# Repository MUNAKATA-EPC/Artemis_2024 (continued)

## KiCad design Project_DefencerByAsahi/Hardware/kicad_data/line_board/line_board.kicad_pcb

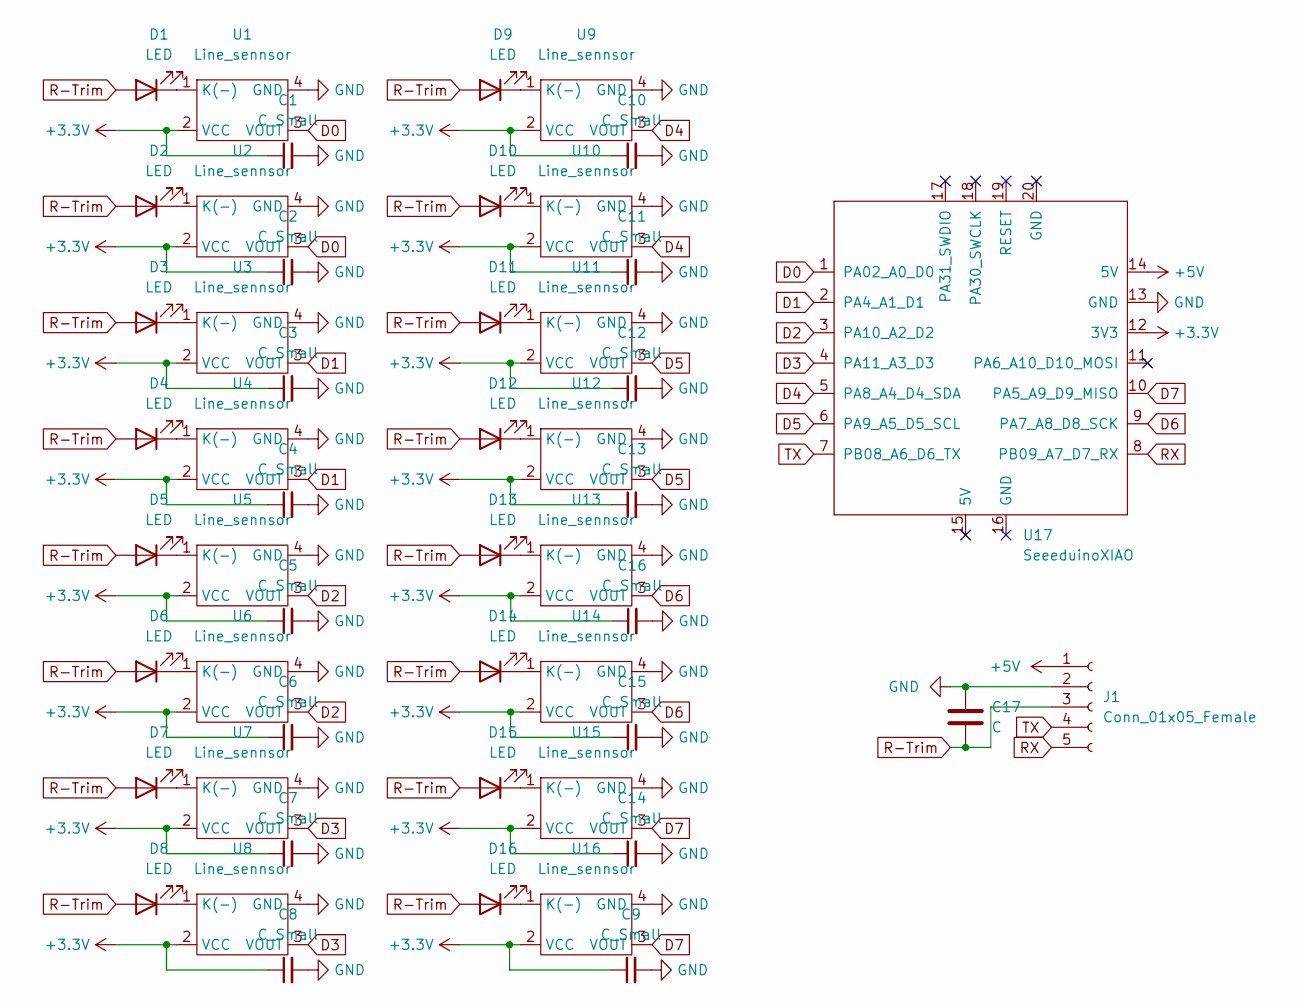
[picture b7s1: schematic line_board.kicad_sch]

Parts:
C1, C2, C3, C4, C5, C6, C7, C8, C9, C10, C11, C12, C13, C14, C15, C16: C_Small; C_Disc_D3.8mm_W2.6mm_P2.50mm
C17: C; CP_Radial_D5.0mm_P2.50mm
D1, D2, D3, D4, D5, D6, D7, D8, D9, D10, D11, D12, D13, D14, D15, D16: LED; LED_D3.0mm_Clear
J1: Conn_01x05_Female; JST_XH_B5B-XH-A_1x05_P2.50mm_Vertical
U1, U2, U3, U4, U5, U6, U7, U8, U9, U10, U11, U12, U13, U14, U15, U16: Line_sennsor; Line_Sensor
U17: SeeeduinoXIAO; seeeduinoXIAO

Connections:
+3.3V: C1.1, C2.1, C3.1, C4.1, C5.1, C6.1, C7.1, C8.1, C9.1, C10.1, C11.1, C12.1, C13.1, C14.1, C15.1, C16.1, U1.2 (VCC), U2.2 (VCC), U3.2 (VCC), U4.2 (VCC), U5.2 (VCC), U6.2 (VCC), U7.2 (VCC), U8.2 (VCC), U9.2 (VCC), U10.2 (VCC), U11.2 (VCC), U12.2 (VCC), U13.2 (VCC), U14.2 (VCC), U15.2 (VCC), U16.2 (VCC), U17.12 (3V3)
+5V: J1.1, U17.14 (5V)
D0: U1.3 (VOUT), U2.3 (VOUT), U17.1 (PA02_A0_D0)
D1: U3.3 (VOUT), U4.3 (VOUT), U17.2 (PA4_A1_D1)
D2: U5.3 (VOUT), U6.3 (VOUT), U17.3 (PA10_A2_D2)
D3: U7.3 (VOUT), U8.3 (VOUT), U17.4 (PA11_A3_D3)
D4: U9.3 (VOUT), U10.3 (VOUT), U17.5 (PA8_A4_D4_SDA)
D5: U11.3 (VOUT), U12.3 (VOUT), U17.6 (PA9_A5_D5_SCL)
D6: U13.3 (VOUT), U14.3 (VOUT), U17.9 (PA7_A8_D8_SCK)
D7: U15.3 (VOUT), U16.3 (VOUT), U17.10 (PA5_A9_D9_MISO)
GND: C1.2, C2.2, C3.2, C4.2, C5.2, C6.2, C7.2, C8.2, C9.2, C10.2, C11.2, C12.2, C13.2, C14.2, C15.2, C16.2, C17.1, J1.2, U1.4 (GND), U2.4 (GND), U3.4 (GND), U4.4 (GND), U5.4 (GND), U6.4 (GND), U7.4 (GND), U8.4 (GND), U9.4 (GND), U10.4 (GND), U11.4 (GND), U12.4 (GND), U13.4 (GND), U14.4 (GND), U15.4 (GND), U16.4 (GND), U17.13 (GND)
unnamed: D1.1 (K), U1.1 (K(-))
unnamed: D2.1 (K), U2.1 (K(-))
unnamed: D3.1 (K), U3.1 (K(-))
unnamed: D4.1 (K), U4.1 (K(-))
unnamed: D5.1 (K), U5.1 (K(-))
unnamed: D6.1 (K), U6.1 (K(-))
unnamed: D7.1 (K), U7.1 (K(-))
unnamed: D8.1 (K), U8.1 (K(-))
unnamed: D9.1 (K), U9.1 (K(-))
unnamed: D10.1 (K), U10.1 (K(-))
unnamed: D11.1 (K), U11.1 (K(-))
unnamed: D12.1 (K), U12.1 (K(-))
unnamed: D13.1 (K), U13.1 (K(-))
unnamed: D14.1 (K), U14.1 (K(-))
unnamed: D15.1 (K), U15.1 (K(-))
unnamed: D16.1 (K), U16.1 (K(-))
R-Trim: C17.2, D1.2 (A), D2.2 (A), D3.2 (A), D4.2 (A), D5.2 (A), D6.2 (A), D7.2 (A), D8.2 (A), D9.2 (A), D10.2 (A), D11.2 (A), D12.2 (A), D13.2 (A), D14.2 (A), D15.2 (A), D16.2 (A), J1.3
RX: J1.5, U17.8 (PB09_A7_D7_RX)
TX: J1.4, U17.7 (PB08_A6_D6_TX)

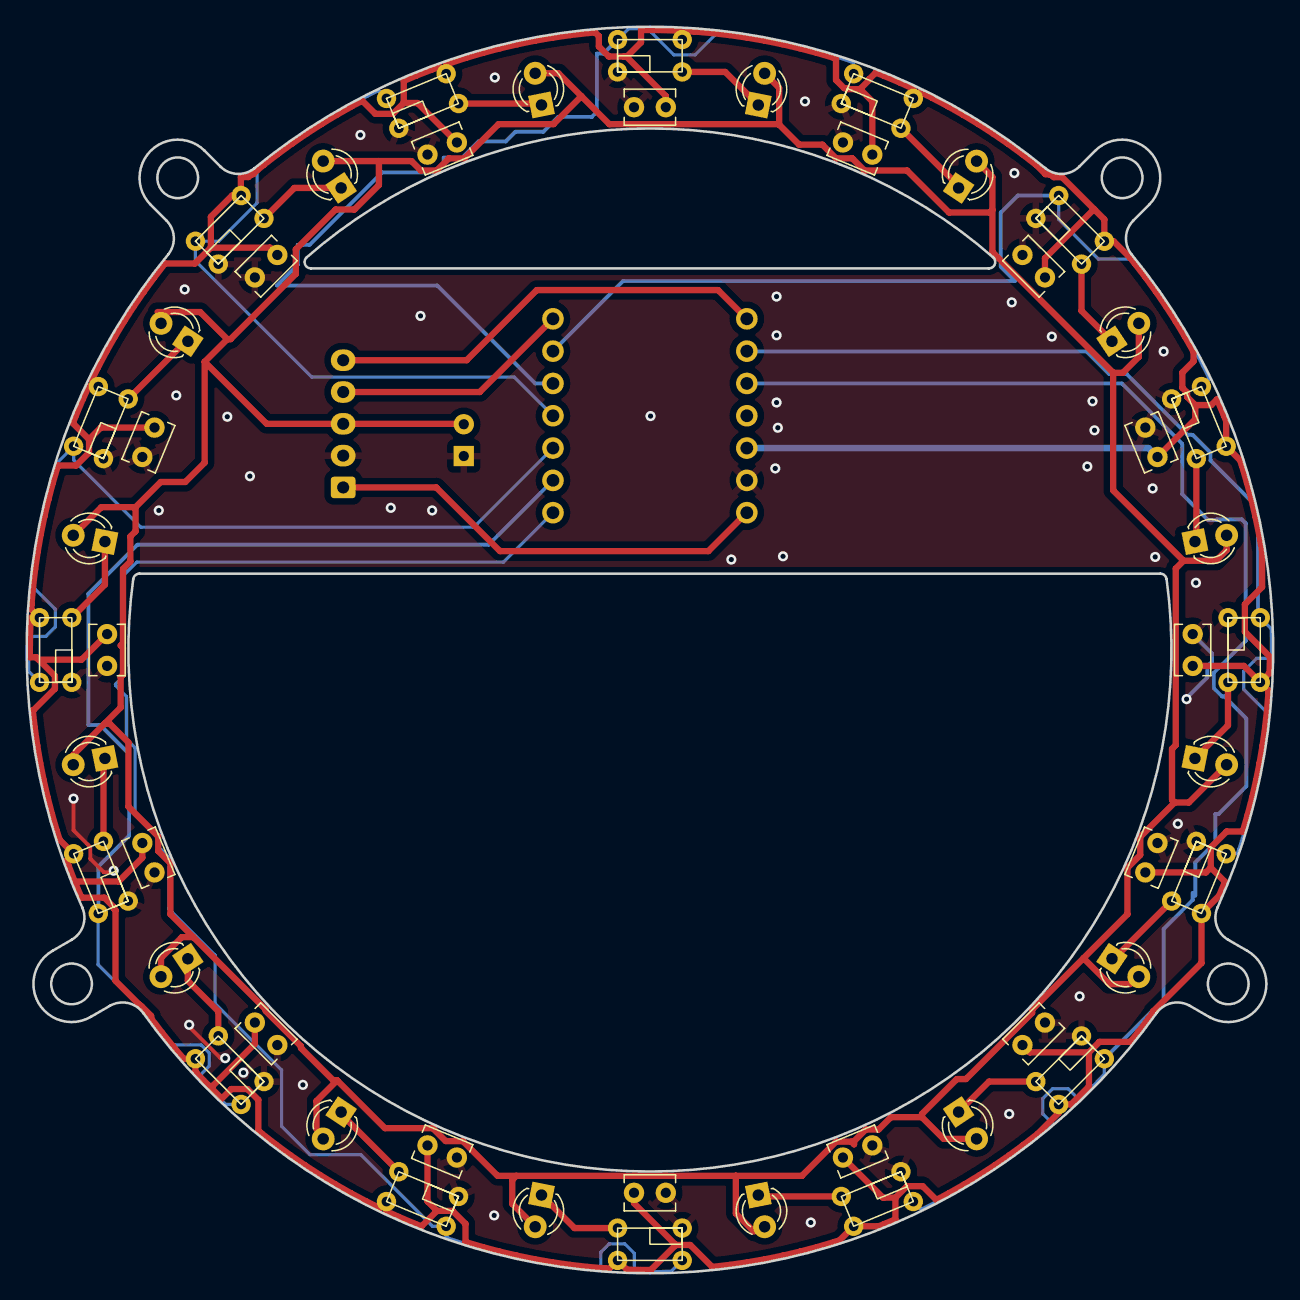
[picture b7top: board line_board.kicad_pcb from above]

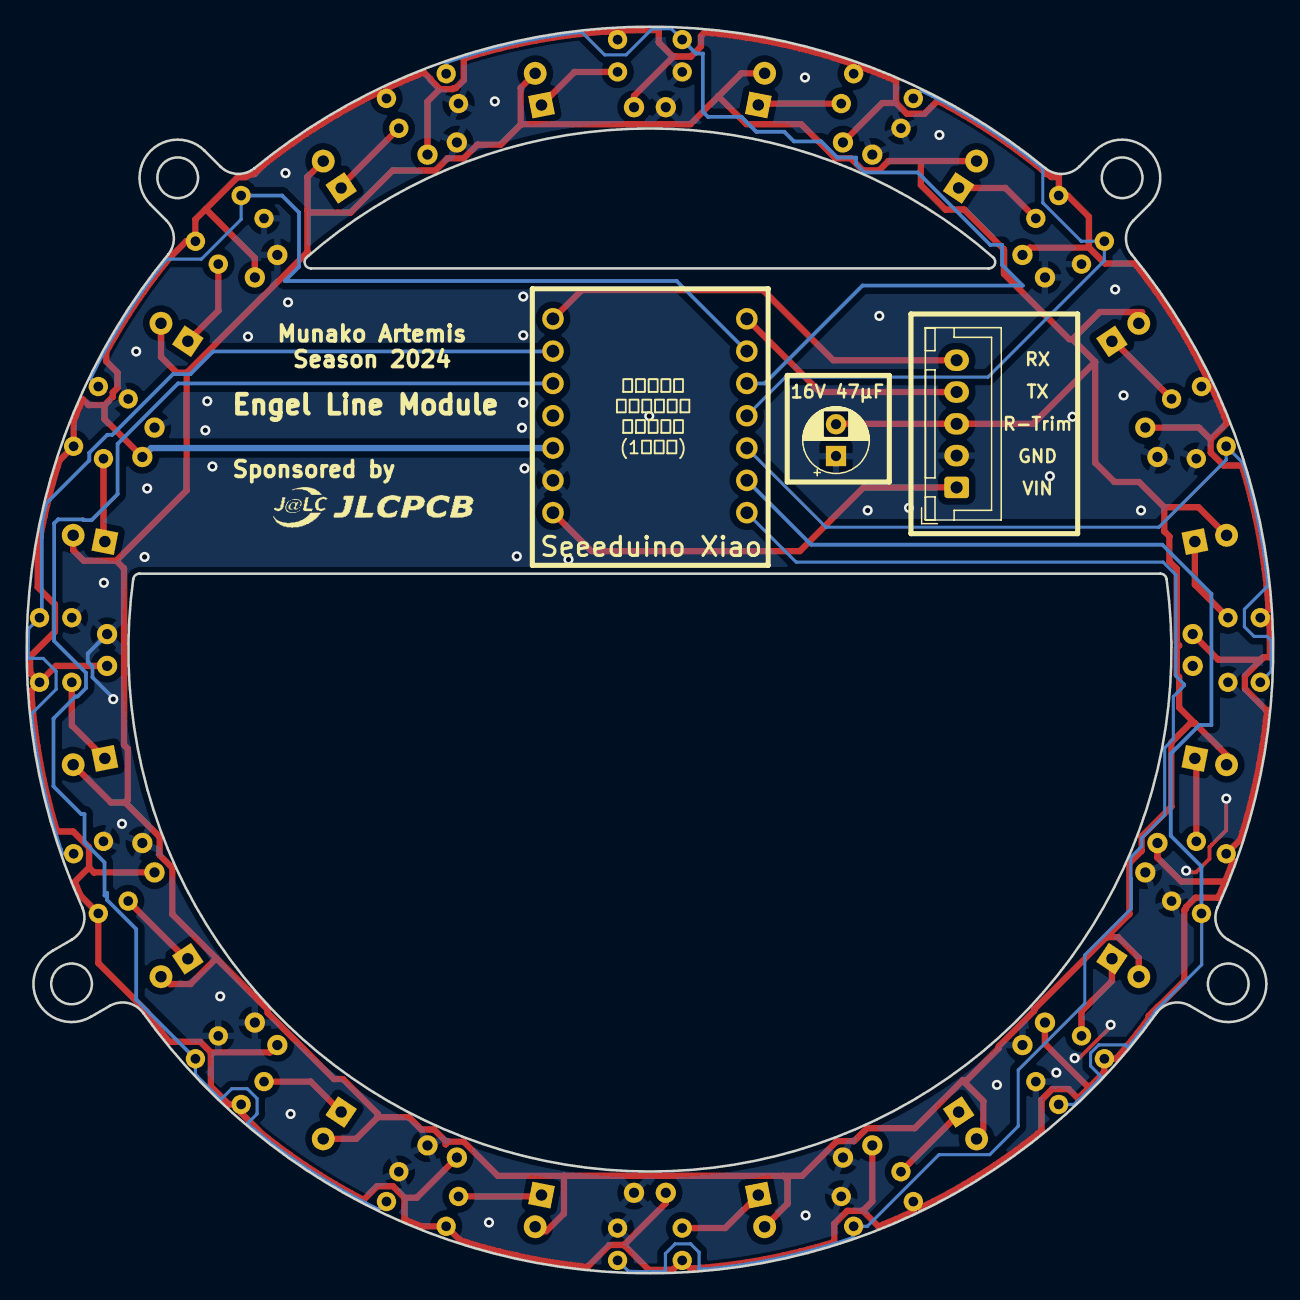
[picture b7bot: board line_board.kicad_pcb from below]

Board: 2 copper layers, 98.0 x 98.0 mm, 51 parts (3 on the bottom side), 30 nets.

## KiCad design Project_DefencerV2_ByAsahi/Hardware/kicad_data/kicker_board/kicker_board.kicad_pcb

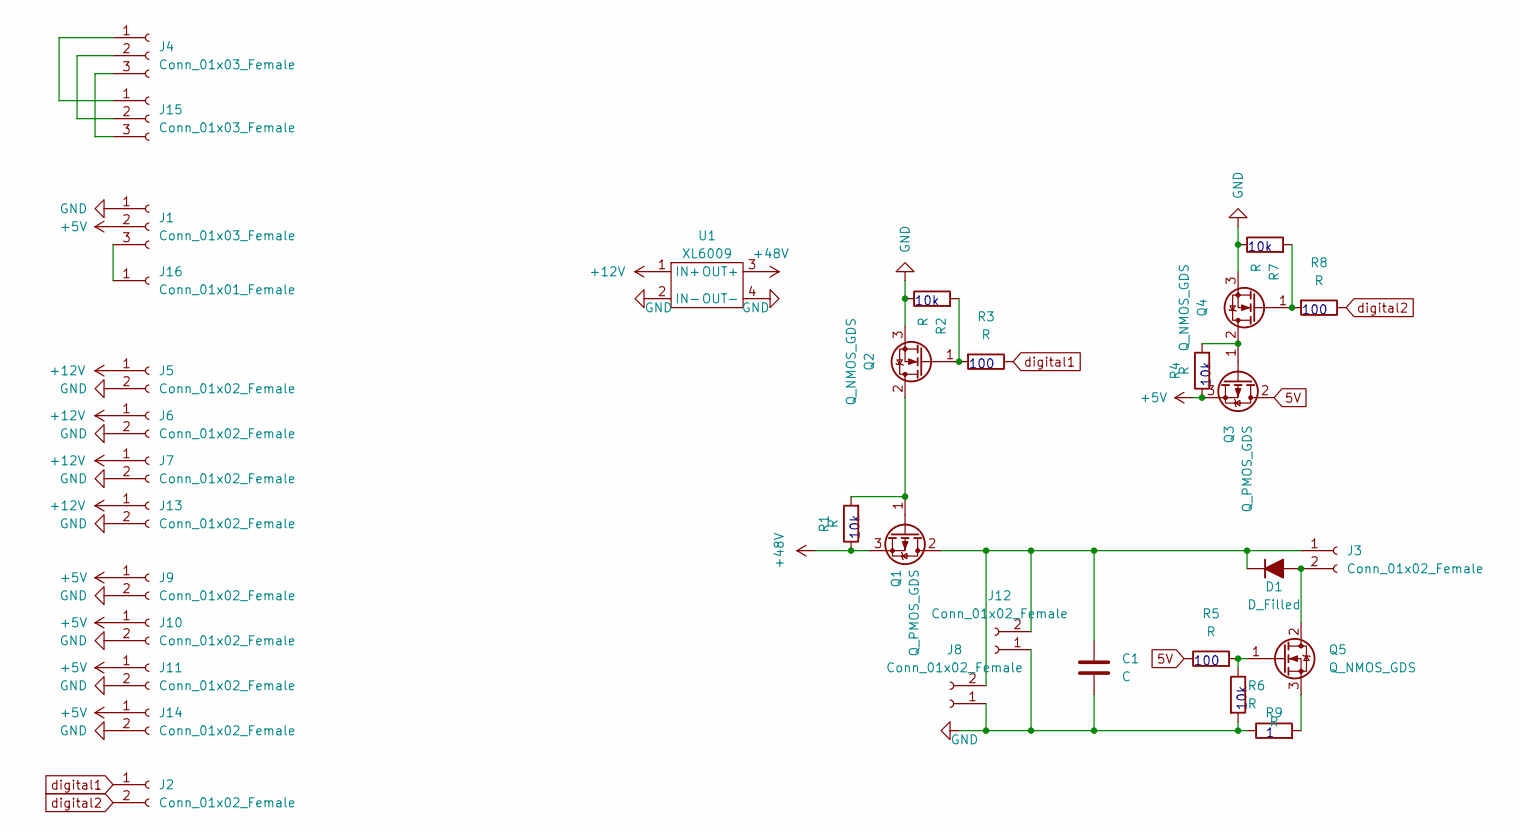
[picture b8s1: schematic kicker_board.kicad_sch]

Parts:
C1: C; CP_Radial_D22.0mm_P10.00mm_SnapIn
D1: D_Filled; D_DO-15_P10.16mm_Horizontal
J1, J4, J15: Conn_01x03_Female; PinHeader_1x03_P2.54mm_Vertical
J2, J3, J5, J6, J7, J8, J9, J10, J11, J12, J13, J14: Conn_01x02_Female; PinHeader_1x02_P2.54mm_Vertical
J16: Conn_01x01_Female; PinHeader_1x01_P2.54mm_Vertical
Q1: Q_PMOS_GDS; Pch MOSFET
Q2, Q4: Q_NMOS_GDS; Nch MOSFET
Q3: Q_PMOS_GDS; Nch MOSFET
Q5: Q_NMOS_GDS; Pch MOSFET
R1, R2, R3, R4, R5, R6, R7, R8: R; R_Axial_DIN0207_L6.3mm_D2.5mm_P7.62mm_Horizontal
R9: R; R_Axial_Power_L20.0mm_W6.4mm_P5.08mm_Vertical
U1: XL6009

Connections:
5V: Q3.2 (D), R5.1
+5V: J1.2, J9.1, J10.1, J11.1, J14.1, Q3.3 (S), R4.1
+12V: J5.1, J6.1, J7.1, J13.1, U1.1 (IN+)
+48V: Q1.3 (S), R1.1, U1.3 (OUT+)
GND: C1.2, J1.1, J5.2, J6.2, J7.2, J8.1, J9.2, J10.2, J11.2, J12.1, J13.2, J14.2, Q2.3 (S), Q4.3 (S), R2.1, R6.2, R7.1, R9.1, U1.2 (IN-), U1.4 (OUT-)
unnamed: C1.1, D1.1 (K), J3.1, J8.2, J12.2, Q1.2 (D)
unnamed: D1.2 (A), J3.2, Q5.2 (D)
unnamed: J1.3, J16.1
unnamed: J4.1, J15.1
unnamed: J4.2, J15.2
unnamed: J4.3, J15.3
unnamed: Q1.1 (G), Q2.2 (D), R1.2
unnamed: Q2.1 (G), R2.2, R3.2
unnamed: Q3.1 (G), Q4.2 (D), R4.2
unnamed: Q4.1 (G), R7.2, R8.2
unnamed: Q5.1 (G), R5.2, R6.1
unnamed: Q5.3 (S), R9.2
digital1: J2.1, R3.1
digital2: J2.2, R8.1

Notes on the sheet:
10k
100

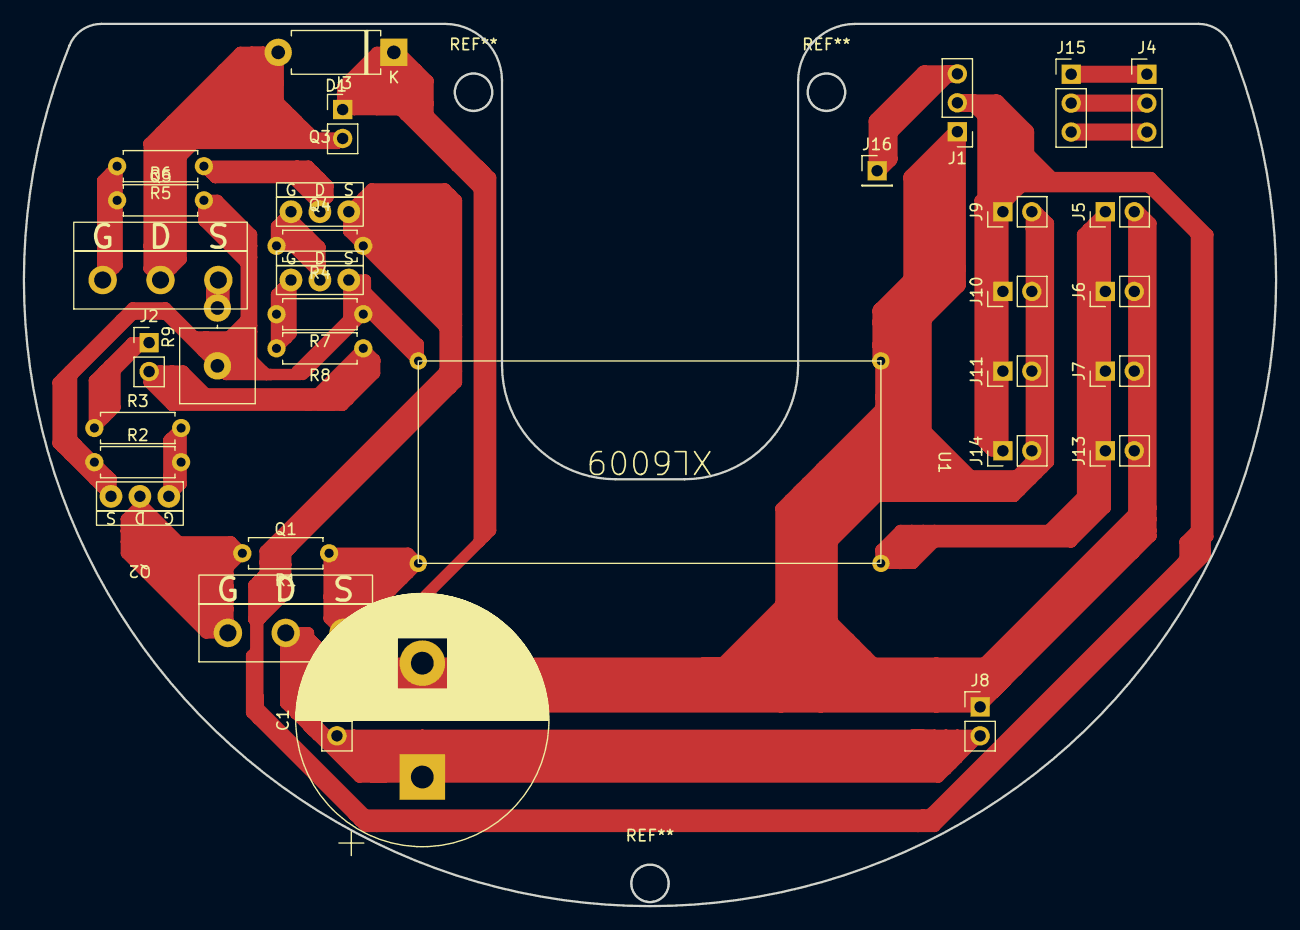
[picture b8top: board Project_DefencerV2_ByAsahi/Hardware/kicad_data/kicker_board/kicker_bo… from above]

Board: 2 copper layers, 110.0 x 77.5 mm, 33 parts (0 on the bottom side), 19 nets.

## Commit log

2024-12-10 We are Munako Artemis.
